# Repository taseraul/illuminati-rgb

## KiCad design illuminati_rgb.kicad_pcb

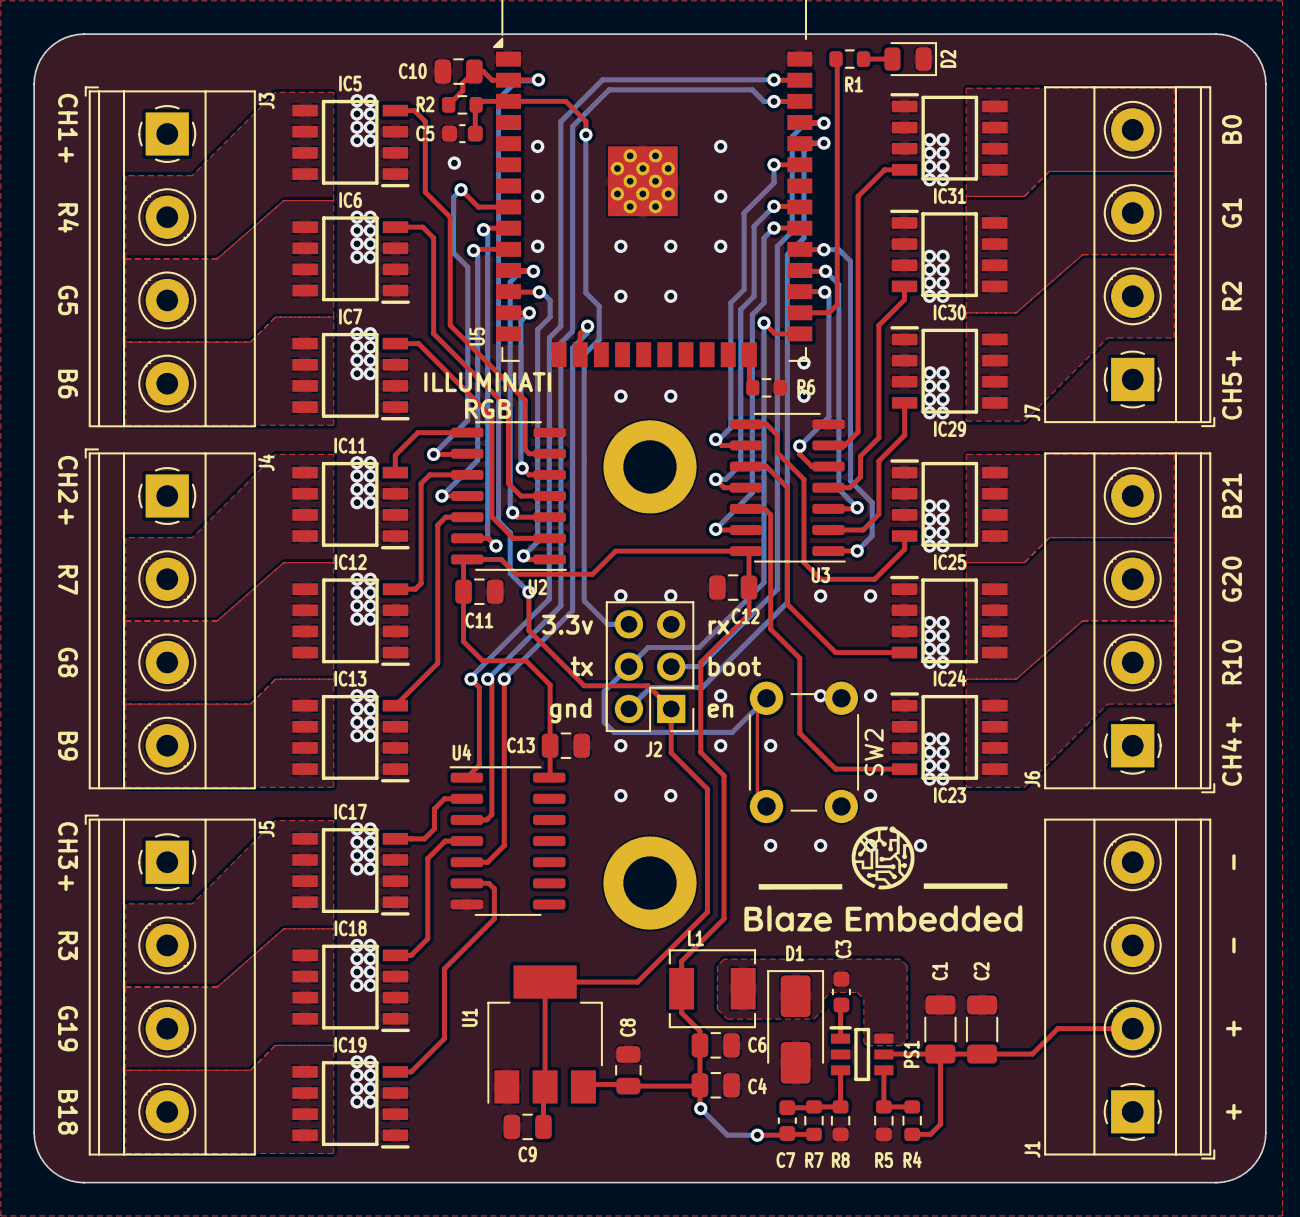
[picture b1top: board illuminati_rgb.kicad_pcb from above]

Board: 2 copper layers, 74.0 x 69.0 mm, 54 parts (0 on the bottom side), 60 nets.

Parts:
C1, C2: 10u/1206; C_1206_3216Metric
C3: 22n; C_0603_1608Metric
C4, C6, C8, C9, C10, C11, C12, C13: 22u; C_0805_2012Metric
C5: 100n; C_0603_1608Metric
C7: 100p; C_0603_1608Metric
D1: B340A; D_SMA
D2: LED; LED_0805_2012Metric
H1, H2: MountingHole_Pad; MountingHole_3.2mm_M3_DIN965_Pad
IC5, IC6, IC7, IC11, IC12, IC13, IC17, IC18, IC19, IC23, IC24, IC25, IC29, IC30, IC31: SI4174DY-T1-GE3; SOIC127P600X175-8N
J1, J3, J4, J5, J6, J7: Conn_01x04; TerminalBlock_Phoenix_MKDS-1,5-4_1x04_P5.00mm_Horizontal
J2: Conn_02x03_Odd_Even; PinHeader_2x03_P2.54mm_Vertical
L1: 10u/C2921170; L_Chilisin_BMRA00040420
PS1: AP5100WG-7; SOT95P285X140-6N
R1, R5, R8: 2k; R_0603_1608Metric
R2, R4, R6, R7: 10k; R_0603_1608Metric
SW2: SW_SPST; SW_PUSH_6mm_H8mm
U1: AMS1117-3.3; SOT-223-3_TabPin2
U2, U3, U4: 74HC14; SOIC-14_3.9x8.7mm_P1.27mm
U5: ESP32-WROOM-32

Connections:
+3V3: C9.1, C10.1, J2.1, R2.1, U1.2 (VO), U5.2 (VDD)
+5V: C4.1, C6.1, C7.1, C8.1, C11.1, C12.1, C13.1, L1.2, R7.1, U1.3 (VI), U2.14 (VCC), U3.14 (VCC), U4.14 (VCC)
/B1: U2.1, U5.12 (IO27)
/B2: U2.13, U5.9 (IO33)
/B3: U4.5, U5.16 (IO13)
/B4: U3.9, U5.33 (IO21)
/B5: U3.5, U5.27 (IO16)
/G1: U2.3, U5.11 (IO26)
/G2: U2.11, U5.10 (IO25)
/G3: U4.3, U5.36 (IO22)
/G4: U3.11, U5.31 (IO19)
/G5: U3.3, U5.28 (IO17)
/R1: U2.5, U5.13 (IO14)
/R2: U2.9, U5.8 (IO32)
/R3: U4.1, U5.37 (IO23)
/R4: U3.13, U5.30 (IO18)
/R5: U3.1, U5.29 (IO5)
/RGB Channel1/B: IC7.4 (G), U2.2
/RGB Channel1/G: IC6.4 (G), U2.4
/RGB Channel1/OUT_B: IC7.5 (D_1), IC7.6 (D_2), IC7.7 (D_3), IC7.8 (D_4), J3.4
/RGB Channel1/OUT_G: IC6.5 (D_1), IC6.6 (D_2), IC6.7 (D_3), IC6.8 (D_4), J3.3
/RGB Channel1/OUT_R: IC5.5 (D_1), IC5.6 (D_2), IC5.7 (D_3), IC5.8 (D_4), J3.2
/RGB Channel1/R: IC5.4 (G), U2.6
/RGB Channel2/B: IC13.4 (G), U2.12
/RGB Channel2/G: IC12.4 (G), U2.10
/RGB Channel2/OUT_B: IC13.5 (D_1), IC13.6 (D_2), IC13.7 (D_3), IC13.8 (D_4), J4.4
/RGB Channel2/OUT_G: IC12.5 (D_1), IC12.6 (D_2), IC12.7 (D_3), IC12.8 (D_4), J4.3
/RGB Channel2/OUT_R: IC11.5 (D_1), IC11.6 (D_2), IC11.7 (D_3), IC11.8 (D_4), J4.2
/RGB Channel2/R: IC11.4 (G), U2.8
/RGB Channel3/B: IC19.4 (G), U4.6
/RGB Channel3/G: IC18.4 (G), U4.4
/RGB Channel3/OUT_B: IC19.5 (D_1), IC19.6 (D_2), IC19.7 (D_3), IC19.8 (D_4), J5.4
/RGB Channel3/OUT_G: IC18.5 (D_1), IC18.6 (D_2), IC18.7 (D_3), IC18.8 (D_4), J5.3
/RGB Channel3/OUT_R: IC17.5 (D_1), IC17.6 (D_2), IC17.7 (D_3), IC17.8 (D_4), J5.2
/RGB Channel3/R: IC17.4 (G), U4.2
/RGB Channel4/B: IC25.4 (G), U3.8
/RGB Channel4/G: IC24.4 (G), U3.10
/RGB Channel4/OUT_B: IC25.5 (D_1), IC25.6 (D_2), IC25.7 (D_3), IC25.8 (D_4), J6.4
/RGB Channel4/OUT_G: IC24.5 (D_1), IC24.6 (D_2), IC24.7 (D_3), IC24.8 (D_4), J6.3
/RGB Channel4/OUT_R: IC23.5 (D_1), IC23.6 (D_2), IC23.7 (D_3), IC23.8 (D_4), J6.2
/RGB Channel4/R: IC23.4 (G), U3.12
/RGB Channel5/B: IC31.4 (G), U3.6
/RGB Channel5/G: IC30.4 (G), U3.4
/RGB Channel5/OUT_B: IC31.5 (D_1), IC31.6 (D_2), IC31.7 (D_3), IC31.8 (D_4), J7.4
/RGB Channel5/OUT_G: IC30.5 (D_1), IC30.6 (D_2), IC30.7 (D_3), IC30.8 (D_4), J7.3
/RGB Channel5/OUT_R: IC29.5 (D_1), IC29.6 (D_2), IC29.7 (D_3), IC29.8 (D_4), J7.2
/RGB Channel5/R: IC29.4 (G), U3.2
/V_FB: C7.2, PS1.3 (FB), R7.2, R8.1
/boot: J2.4, SW2.2 (B), U5.25 (IO0)
/esp_en: C5.1, J2.6, R2.2, U5.3 (EN)
/rx: J2.2, U5.34 (RXD0/IO3)
/tx: J2.3, U5.35 (TXD0/IO1)
GND: C1.2, C2.2, C4.2, C5.2, C6.2, C8.2, C9.2, C10.2, C11.2, C12.2, C13.2, D1.2 (A), D2.1 (K), H1.1, H2.1, IC5.1 (S_1), IC5.2 (S_2), IC5.3 (S_3), IC6.1 (S_1), IC6.2 (S_2), IC6.3 (S_3), IC7.1 (S_1), IC7.2 (S_2), IC7.3 (S_3), IC11.1 (S_1), IC11.2 (S_2), IC11.3 (S_3), IC12.1 (S_1), IC12.2 (S_2), IC12.3 (S_3), IC13.1 (S_1), IC13.2 (S_2), IC13.3 (S_3), IC17.1 (S_1), IC17.2 (S_2), IC17.3 (S_3), IC18.1 (S_1), IC18.2 (S_2), IC18.3 (S_3), IC19.1 (S_1), IC19.2 (S_2), IC19.3 (S_3), IC23.1 (S_1), IC23.2 (S_2), IC23.3 (S_3), IC24.1 (S_1), IC24.2 (S_2), IC24.3 (S_3), IC25.1 (S_1), IC25.2 (S_2), IC25.3 (S_3), IC29.1 (S_1), IC29.2 (S_2), IC29.3 (S_3), IC30.1 (S_1), IC30.2 (S_2), IC30.3 (S_3), IC31.1 (S_1), IC31.2 (S_2), IC31.3 (S_3), J1.3, J1.4, J2.5, PS1.2 (GND), R5.1, R6.2, R8.2, SW2.1 (A), U1.1 (GND), U2.7 (GND), U3.7 (GND), U4.7 (GND), U5.1 (GND), U5.15 (GND), U5.38 (GND), U5.39 (GND)
unnamed: C3.2, D1.1 (K), L1.1, PS1.6 (SW)
unnamed: D2.2 (A), R1.2
unnamed: C3.1, PS1.1 (BST)
unnamed: PS1.4 (EN), R4.1, R5.2
unnamed: R6.1, U5.24 (IO2)
unnamed: R1.1, U5.26 (IO4)
VCC: C1.1, C2.1, J1.1, J1.2, J3.1, J4.1, J5.1, J6.1, J7.1, PS1.5 (IN), R4.2

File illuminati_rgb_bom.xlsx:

Comment | Designator | Footprint | JLCPCB Part #（optional）
10k | R2,R1,R6,R3,R4,R7 | R_0603_1608Metric | C25804
22u | C12,C8,C6,C11,C4,C10,C9,C13 | C_0805_2012Metric | C45783
74HC14 | U4,U3,U2 | SOIC-14_3.9x8.7mm_P1.27mm | C5605
SI4174DY-T1-GE3 | IC13,IC19,IC30,IC31,IC7,IC18,IC5,IC17,IC29,IC25,IC23,IC6,IC12,IC24,IC11 | SOIC127P600X175-8N | C496589
Conn_01x04 | J4,J1,J7,J6,J5,J3 | TerminalBlock_Phoenix_MKDS-1,5-4_1x04_P5.00mm_Horizontal | C192769
B340A | D1 | D_SMA | C3018525
100n | C5 | C_0603_1608Metric | C14663
2k | R8,R5 | R_0603_1608Metric | C22975
AMS1117-3.3 | U1 | SOT-223-3_TabPin2 | C6186
10u/1206 | C1,C2 | C_1206_3216Metric | C13585
AP5100WG-7 | PS1 | SOT95P285X140-6N | C114647
100p | C7 | C_0603_1608Metric | C1790
10u/C2921170 | L1 | L_Chilisin_BMRA00040420 | C2921170
22n | C3 | C_0603_1608Metric | C21122

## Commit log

2024-02-19 v2 board
2024-07-07 V2.1 swap esp32c3 for esp32 and change form factor
